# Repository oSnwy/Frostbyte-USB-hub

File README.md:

# Frostbyte USB Hub

A custom icy-themed USB 2.0 hub with USB-C and USB-A ports, built around the SL2.1A hub controller and packaged in a custom 3D-printed case.

The name "Frostbyte" started as a play on byte and my username, and how winter themed things are pretty cool. No pun intended hehe. The case itself is intentionally simple: a compact rectangular enclosure with rounded edges, designed to look clean on a desk instead of drawing too much attention. The "frost" part is less about making the case look like ice and more about the clean, minimal, cool-toned design direction I wanted for the project, and keeps it compact and easy to print, as well as matches the naming scheme of some of my other projects.

### Design Goals

- Keep the hub compact enough for a desk setup
- Support both USB-C and USB-A devices
- Use a more stable external clock source
- Make the case feel like a finished product, not just a project box
- Keep the PCB easy to assemble and debug

</p> 

|  |  |  |
| - | - | - |

## What is this?

Frostbyte was my introductory project into more complicated PCB design. I wanted to make a USB hub that felt more like a finished desk accessory than a bare PCB, while also reducing cable clutter on my desk. The goal was to make one compact dock where I could plug in my everyday accessories instead of having wires spread everywhere.

Although Frostbyte is based on the Macondo USB hub tutorial, I wanted to make the design my own instead of blindly copying the guide. I changed the port layout, added an external 12 MHz crystal for more stable USB timing, used parallel 0.1 uF and 10 uF decoupling capacitors for cleaner power, and designed a custom 3D-printed case around the PCB.

The hub has one upstream USB-C port, two downstream USB-C ports, and two downstream USB-A ports, all fit into a custom case designed to match the "Frostbyte" theme.

### Engineering Choices

Some of the design choices I made were less about adding flashy features and more about making the hub stable and manufacturable. I used an external 12 MHz crystal for the SL2.1A, added local decoupling capacitors near the power rails, and designed the case around actual PCB mounting points instead of making the enclosure as an afterthought. The case, designed to be minimalist, was also designed to be easily printed in two parts without overhangs or needs for supports, as well as easily assebmled with minimal effort.

## Challenges

One of the hardest parts was balancing the electronics and the enclosure. The USB ports had to line up with the case openings, the PCB needed enough clearance inside the shell, and the case still had to be printable. I also had to learn more about USB 2.0 routing, especially keeping the differential pairs clean and making sure the crystal and capacitors were placed properly. I also needed to make sure the routing was clean and without mistakes, with each DN and DP pair containing traces close together.

### Features:

- 1 upstream USB-C port
- 2 downstream USB-C ports
- 2 downstream USB-A ports
- SL2.1A USB 2.0 hub controller
- External 12 MHz crystal for more reliable USB timing
- Parallel 0.1 uF and 10 uF decoupling capacitors for cleaner power
- Custom PCB designed for the Macondo project
- Custom 3D-printed case with a press-fit design
- PCB mounts into the bottom case using M2 screws

### What I Changed From the Tutorial

- Used a custom port layout with both USB-C and USB-A downstream ports
- Added an external 12 MHz crystal for the SL2.1A
- Used parallel 0.1 uF and 10 uF decoupling capacitors on the power rails
- Designed a custom case instead of leaving the PCB exposed
- Planned the PCB mounting around M2 screws and a press-fit enclosure

### Notes / Limitations

This is a USB 2.0 hub, not a USB 3.0 hub. It is designed for normal peripherals like keyboards, mice, flash drives, and small USB accessories, not high-power charging. DO NOT USE for alternate purposes (I'm not responsible if you blow up your laptop!!).

### Future Improvements

If I made another version, I would increase the number of ports, as the two USB-A and USB-C ports may not be enough for future accessories. Additionally, I would add a power delivery port, allowing high-speed charging through the USB hub for other applicances. Lastly, I would add a couple of features such as a rotary encoder or macro keys to the hub in order for it to be more than just a USB hub, which may need the addition of a microcontroller.

### What did I learn?

While making Frostbyte, I learned more about USB 2.0 routing, differential pairs, decoupling capacitors, crystal placement, and how much the mechanical design affects the final feel of a hardware project. 
I also improved my skills in different software/tools such as KiCad schematics, PCBs, as well as CAD softwares such as FreeCad and TinkerCad although the final design was done in [OnShape](https://cad.onshape.com/documents/c9b467c6ac72e99f79eebd34/w/909402ed37444c79486434d0/e/d14026541bd022353ba53d64?renderMode=0&uiState=6a5196109ed6ccb7c50ef2e0).

## Assembly Notes

The PCB mounts into the bottom half of the case using M2 screws. The top and bottom case halves are designed to press-fit together, so the hub can stay closed without glue while still being possible to open for debugging or repairs.

ONSHAPE LINK: [OnShape](https://cad.onshape.com/documents/c9b467c6ac72e99f79eebd34/w/909402ed37444c79486434d0/e/d14026541bd022353ba53d64?renderMode=0&uiState=6a5196109ed6ccb7c50ef2e0)

## Quick Specs

| Spec | Details |
| - | - |
| Hub controller | SL2.1A |
| USB version | USB 2.0 |
| Upstream ports | 1x USB-C |
| Downstream ports | 2x USB-C, 2x USB-A |
| Clock source | External 12 MHz crystal |
| Case | Custom 3D-printed press-fit enclosure |
| Mounting | M2 screws |

## What if I want this?
If you want this exact USB hub, just download the [Frostbyte-USB-Hub.zip](https://github.com/oSnwy/Frostbyte-USB-hub/blob/main/Gerber%20Files/frostbyte-USB-Hub.zip) from the Gerber Files folder, as well as the [bom.csv](https://github.com/oSnwy/Frostbyte-USB-hub/blob/main/JLCPCB%20files/bom.csv) and [positions.csv](https://github.com/oSnwy/Frostbyte-USB-hub/blob/main/JLCPCB%20files/positions.csv) from the JLCPCB files folder. Simply upload the files to [JLCPCB's Order Now](https://cart.jlcpcb.com/quote?spm=Jlcpcb.Homepage.1006&spm=Jlcpcb.Homepage.1006), and add these parts below to each footprint or use the links in the BOM below:

</p> 
After that, all you need to do is add it to the cart!

If you'd like to make your own, all the resources I used are linked below! These are some helpful links that can get you started. Alternatively, you can follow my process documented in the journals below!

### PCB AND SCHEMATIC
|  |  |
| - | - | 

### RESOURCES USED: 
| Use | Website Link |
| - | - |
| Macondo Tutorial | [Macondo](https://macondo.hackclub.com/docs/usb-hub) |
| Crystal Example | [Github](https://github.com/xunker/simple_sl2.1a_usb_hub) |
| Crystal Example 2 | [Oshwlab](https://oshwlab.com/oshwlab/USB-concentrator-Based-on-SL2.1A) |
| Crystal Example 3 | [Github](https://github.com/Hugoyhu/SL2.1A-Type-C-Hub) |
| Data Sheet | [LCSC](https://www.lcsc.com/datasheet/C6798314.pdf?spm=wm.sxq.inf.ggs___wm.fly.bg.1.xh&lcsc_vid=EQVWVVVTFAVWAwUDQVkNBFdSRQBZBFJeR1UIBFYHTgUxVlNeRFdcUFFURlRdXjsOAxUeFF5JWBYZEEoKFBINSQcJGk4eFQsCAgIaSgADAwAHC0slRVdWU1BVRE8GEwkK) |
| Footprint and Symbol Download | [SnapEDA](https://www.snapeda.com/parts/SL2.1A/CoreChips%20ShenZhen%20CO.,Ltd/view-part/?company=Maple&amp;welcome=home) |

## TOTAL COST
Total cost, including assembly, comes to around $52.94 CAD from JLCPCB, or $37.32 USD. Attempting to order the PCB without assembly is not recommended due to the difficulty of soldering the crystal and capacitors.

## BOM for PCB
| PART | QTY | LINK |
| - | - | - |
| USB-C Receptacle | 3 | [LINK](https://jlcpcb.com/partdetail/Korean_HropartsElec-TYPE_C_31_M12/C165948) |
| USB-A Receptacle | 2 | [LINK](https://jlcpcb.com/partdetail/MOLEX-676432911/C293351) |
| 12 MHz Crystal | 1 | [LINK](https://jlcpcb.com/partdetail/SST-S503212M20PF20PPMB/C7426819) |
| SL2.1A | 1 | [LINK](https://jlcpcb.com/partdetail/CoreChips-SL21A/C6798314) |
| 4.7R Resistor | 1 | [LINK](https://jlcpcb.com/parts/componentSearch?searchTxt=c23164) |
| 5.1K Resistor | 1 | [LINK](https://jlcpcb.com/parts/componentSearch?searchTxt=c23186) |
| 56K Resistor | 1 |  [LINK](https://jlcpcb.com/partdetail/23933-0603WAF5602T5E/C23206) |
| 10uF Capacitor | 5 | [LINK](https://jlcpcb.com/partdetail/16532-CL21A106KAYNNNE/C15850) |
| 4.7uF Capacitor | 3 | [LINK](https://jlcpcb.com/partdetail/2131-CL21A475KAQNNNE/C1779) |
| 0.1uF Capacitor | 7 | [LINK](https://jlcpcb.com/parts/componentSearch?searchTxt=c14663) |

## JOURNALS

### JOURNAL #1
- July 9th 2026: 2:24 hours
LAPSE LINK: https://lapse.hackclub.com/timelapse/4U5zvK8HuuRQ

</p>

I created the schematic for my USB hub, using 1 USB-C port for upstream, and 2 USB-C ports and 2 USB-A ports for downstream, loosely following the Macondo tutorial and other sources. On top of the tutorial, I added a 12 mHz crystal, tweaked the capacitor and resistor values, and added capacitors in parallel for reliability. In order to figure out the resistor values, I used the original data sheet example, as well as other examples of USB hubs also using the SL2.1A, as the Macondo tutorial used a similar but different SL2.1S. Although they could be wired the same, I wanted to improve upon the tutorial, rather than blindly following it, requiring me to understand each part of the schematic.

</p> 

I also assigned the footprints for the schematic, allowing me to move on to the next step of making the PCB. These parts were found through examples online, as well as the most common parts used.

### JOURNAL #2
- July 9th 2026: 3:10 hours
LAPSE LINK: https://lapse.hackclub.com/timelapse/BneAj1DRkeYR
I started on the creation of the PCB. Despite minor setbacks, such as accidentally assigning the sl2.1a footprint to the capacitor, accidentally using a 4-pin crystal instead of a 2-pin crystal, forgot 0.1uF needs to be close to the pins to make it more effective, putting the usb a ports backwards, needing to put the d+ and d- traces closer and having to move traces away from 12 MHz crystal, majority of the pcb was eventually wired. I had to wire it multiple times to make it both neat and efficient.

</p>
I also created a BOM and CPL for the pieces and positions of the PCB. However, the 12 MHz crystals in the JLCPCB stock didn't match the footprint and needs of my crystal. The next step is to change the footprint of the 12 MHz crystal in order to match a crystal in stock at JLCPCB, as soldering one can be extremely challenging and requires specific tools.

</p>

### JOURNAL #3
LAPSE LINK: https://lapse.hackclub.com/timelapse/NV_NpuBsBBrh

UPDATED PCB:

</p> 
It's done! Despite using the wrong 12 mHz Crystal three times, I finally managed to get the correct footprint and match a correct part onto the board in JLCPCB. I had to edit the PCB a few times and reupload the Gerber files in order for it to work, but it worked out in the end.

Empty PCB:

</p> 
BOM parts:

</p> 
3d Render:

</p> 
Final Price:

</p> 

## JOURNAL #4
LAPSE LINK: https://lapse.hackclub.com/timelapse/RwhSkVn_50UR

</p> 
I created the case for my USB hub. This was created in two parts that snap fit together, with M2 screw standoffs for the PCB to attach to. The PCB is sandwiched between the two parts of the case. This case was designed in TinkerCAD.

## JOURNAL #5
LAPSE LINK: https://lapse.hackclub.com/timelapse/sdaK7IJP7WCH

</p>

</p>
After checking the shipping requirements, it turns out that TinkerCad is not allowed because it doesn't provide the required source files. However, the time spent on TinkerCad was not wasted, as it became an extremely useful reference for 3d modelling on OnShape, as I could use the TinkerCad model for the dimensions, which ended up saving a lot of time. I probably should've read the shipping requirements, but I think using Tinkercad first still saved a little time.

## Journal #6

</p>
I updated the README for GitHub, adding more unique aspects to the design process and build choices, as well as more information specific to the project. I updated the features list, added design goals, added more to the what is this?, added engineering choices and challenges, and listed what I changed from the tutorial. I also added notes and limitations, what I would change if I did it again, as well as the things I learned.

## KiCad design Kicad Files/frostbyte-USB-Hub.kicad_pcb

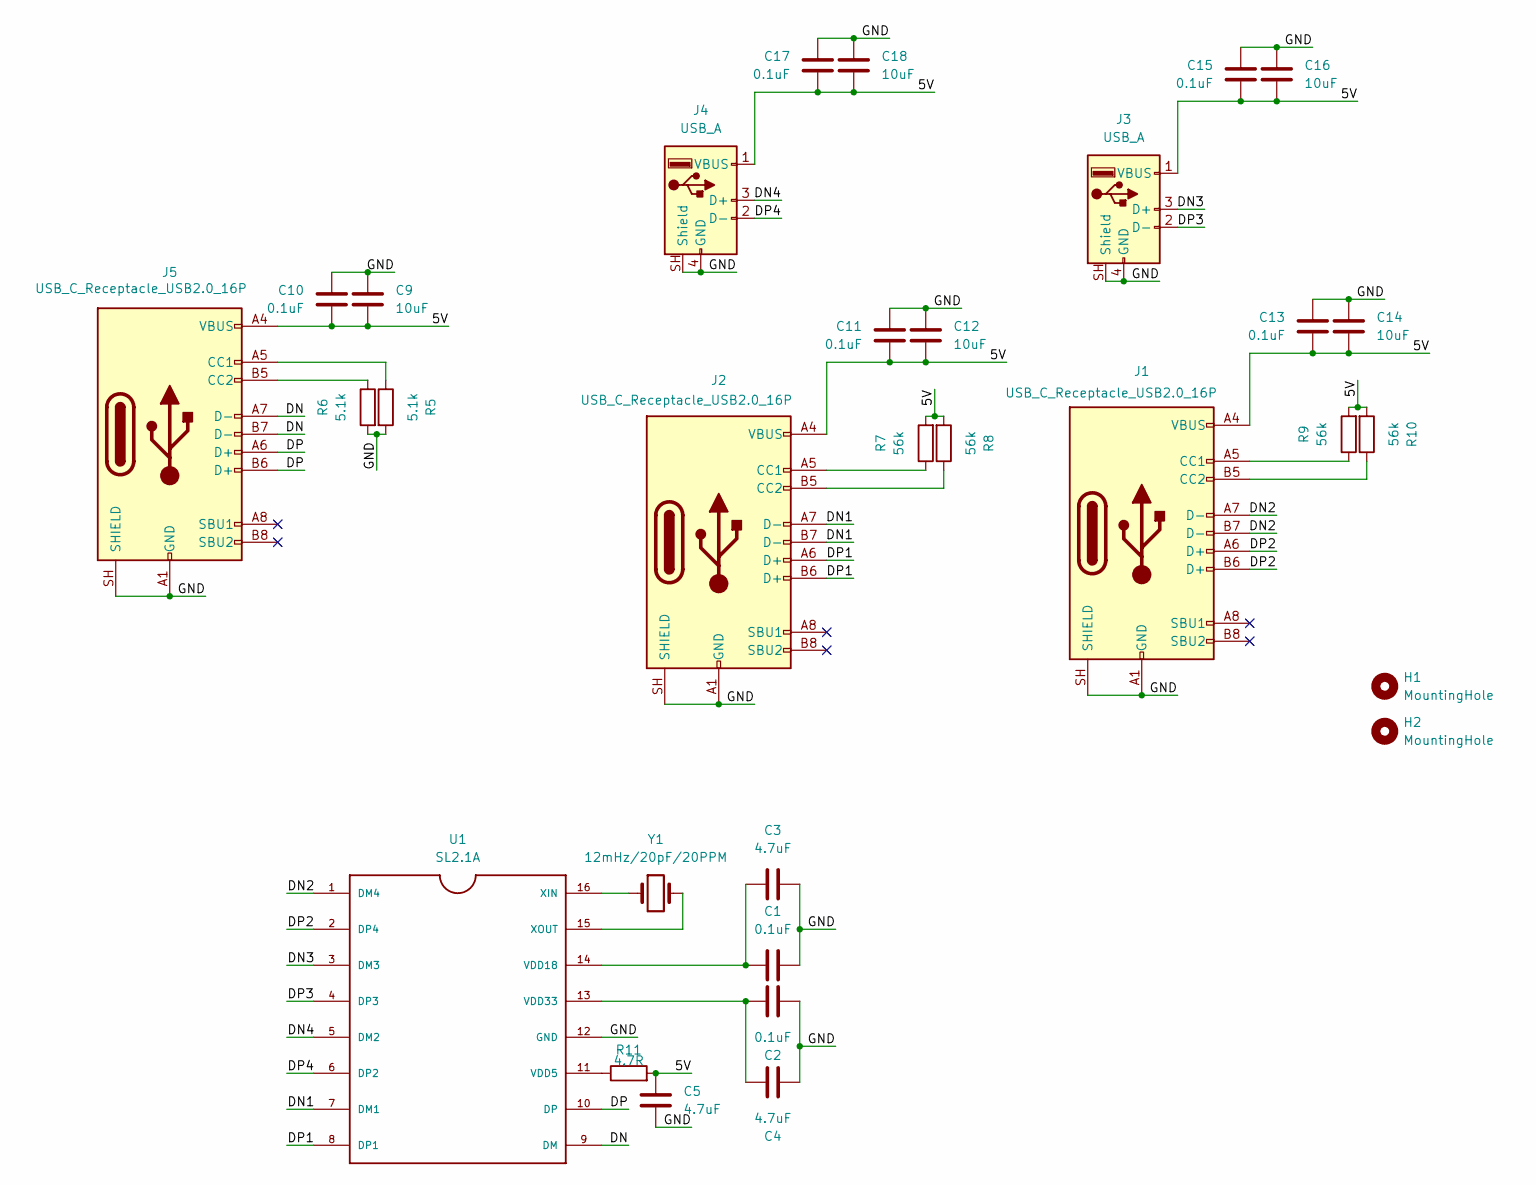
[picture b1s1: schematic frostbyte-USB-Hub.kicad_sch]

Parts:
C1, C2, C10, C11, C13, C15, C17: 0.1uF; C_0603_1608Metric
C3, C4, C5: 4.7uF; C_0805_2012Metric
C9, C12, C14, C16, C18: 10uF; C_0805_2012Metric
H1, H2: MountingHole; MountingHole_2.2mm_M2
J1, J2, J5: USB_C_Receptacle_USB2.0_16P; USB_C_Receptacle_HRO_TYPE-C-31-M-12
J3, J4: USB_A; USB_A_Molex_67643_Horizontal
R5, R6: 5.1k; R_0603_1608Metric
R7, R8, R9, R10: 56k; R_0603_1608Metric
R11: 4.7R; R_0603_1608Metric
U1: SL2.1A; SOIC-16_3.9x9.9mm_P1.27mm
Y1: 12mHz/20pF/20PPM; Crystal_SMD_5032-2Pin_5.0x3.2mm

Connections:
/5V: C5.1, C9.2, C10.2, C11.2, C12.2, C13.2, C14.2, C15.2, C16.2, C17.2, C18.2, J1.A4 (VBUS), J1.A9 (VBUS), J1.B4 (VBUS), J1.B9 (VBUS), J2.A4 (VBUS), J2.A9 (VBUS), J2.B4 (VBUS), J2.B9 (VBUS), J3.1 (VBUS), J4.1 (VBUS), J5.A4 (VBUS), J5.A9 (VBUS), J5.B4 (VBUS), J5.B9 (VBUS), R7.2, R8.2, R9.2, R10.2, R11.2
/DN: J5.A7 (D-), J5.B7 (D-), U1.9 (DM)
/DN1: J2.A7 (D-), J2.B7 (D-), U1.7 (DM1)
/DN2: J1.A7 (D-), J1.B7 (D-), U1.1 (DM4)
/DN3: J3.3 (D+), U1.3 (DM3)
/DN4: J4.3 (D+), U1.5 (DM2)
/DP: J5.A6 (D+), J5.B6 (D+), U1.10 (DP)
/DP1: J2.A6 (D+), J2.B6 (D+), U1.8 (DP1)
/DP2: J1.A6 (D+), J1.B6 (D+), U1.2 (DP4)
/DP3: J3.2 (D-), U1.4 (DP3)
/DP4: J4.2 (D-), U1.6 (DP2)
/GND: C1.2, C2.2, C3.2, C4.2, C5.2, C9.1, C10.1, C11.1, C12.1, C13.1, C14.1, C15.1, C16.1, C17.1, C18.1, J1.A1 (GND), J1.A12 (GND), J1.B1 (GND), J1.B12 (GND), J1.SH (SHIELD), J2.A1 (GND), J2.A12 (GND), J2.B1 (GND), J2.B12 (GND), J2.SH (SHIELD), J3.4 (GND), J3.SH (Shield), J4.4 (GND), J4.SH (Shield), J5.A1 (GND), J5.A12 (GND), J5.B1 (GND), J5.B12 (GND), J5.SH (SHIELD), R5.2, R6.2, U1.12 (GND)
unnamed: J1.A5 (CC1), R9.1
unnamed: J1.B5 (CC2), R10.1
unnamed: J2.A5 (CC1), R7.1
unnamed: J2.B5 (CC2), R8.1
unnamed: J5.A5 (CC1), R5.1
unnamed: J5.B5 (CC2), R6.1
unnamed: R11.1, U1.11 (VDD5)
unnamed: C1.1, C3.1, U1.14 (VDD18)
unnamed: C2.1, C4.1, U1.13 (VDD33)
unnamed: U1.16 (XIN), Y1.1
unnamed: U1.15 (XOUT), Y1.2

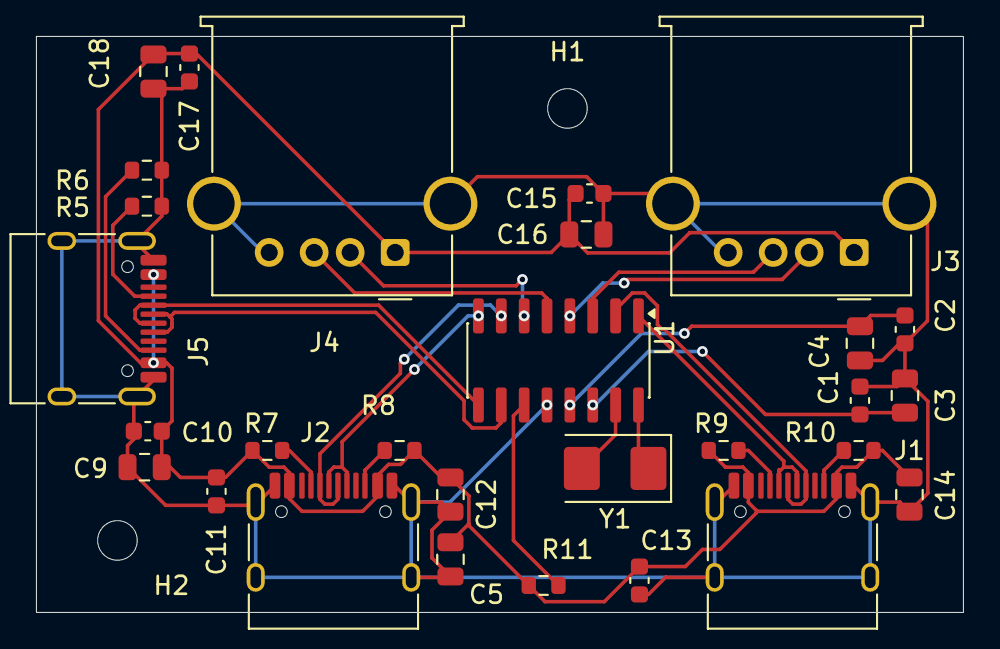
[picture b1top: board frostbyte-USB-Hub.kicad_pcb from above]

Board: 2 copper layers, 51.5 x 32.0 mm, 31 parts (0 on the bottom side), 23 nets.

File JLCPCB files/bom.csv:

Designator,Footprint,Quantity,Value,LCSC Part #
"C1, C10, C11, C13, C15, C17, C2",0603,7,0.1uF,
"C12, C14, C16, C18, C9",0805,5,10uF,
"C3, C4, C5",0805,3,4.7uF,
"J1, J2, J5",USB_C_Receptacle_HRO_TYPE-C-31-M-12,3,USB_C_Receptacle_USB2.0_16P,
"J3, J4",USB_A_Molex_67643_Horizontal,2,USB_A,
"R10, R7, R8, R9",0603,4,56k,
R11,0603,1,4.7R,
"R5, R6",0603,2,5.1k,
U1,SOIC-16_3.9x9.9mm_P1.27mm,1,SL2.1A,
Y1,Crystal_SMD_5032-2Pin_5.0x3.2mm,1,12mHz/20pF/20PPM,
